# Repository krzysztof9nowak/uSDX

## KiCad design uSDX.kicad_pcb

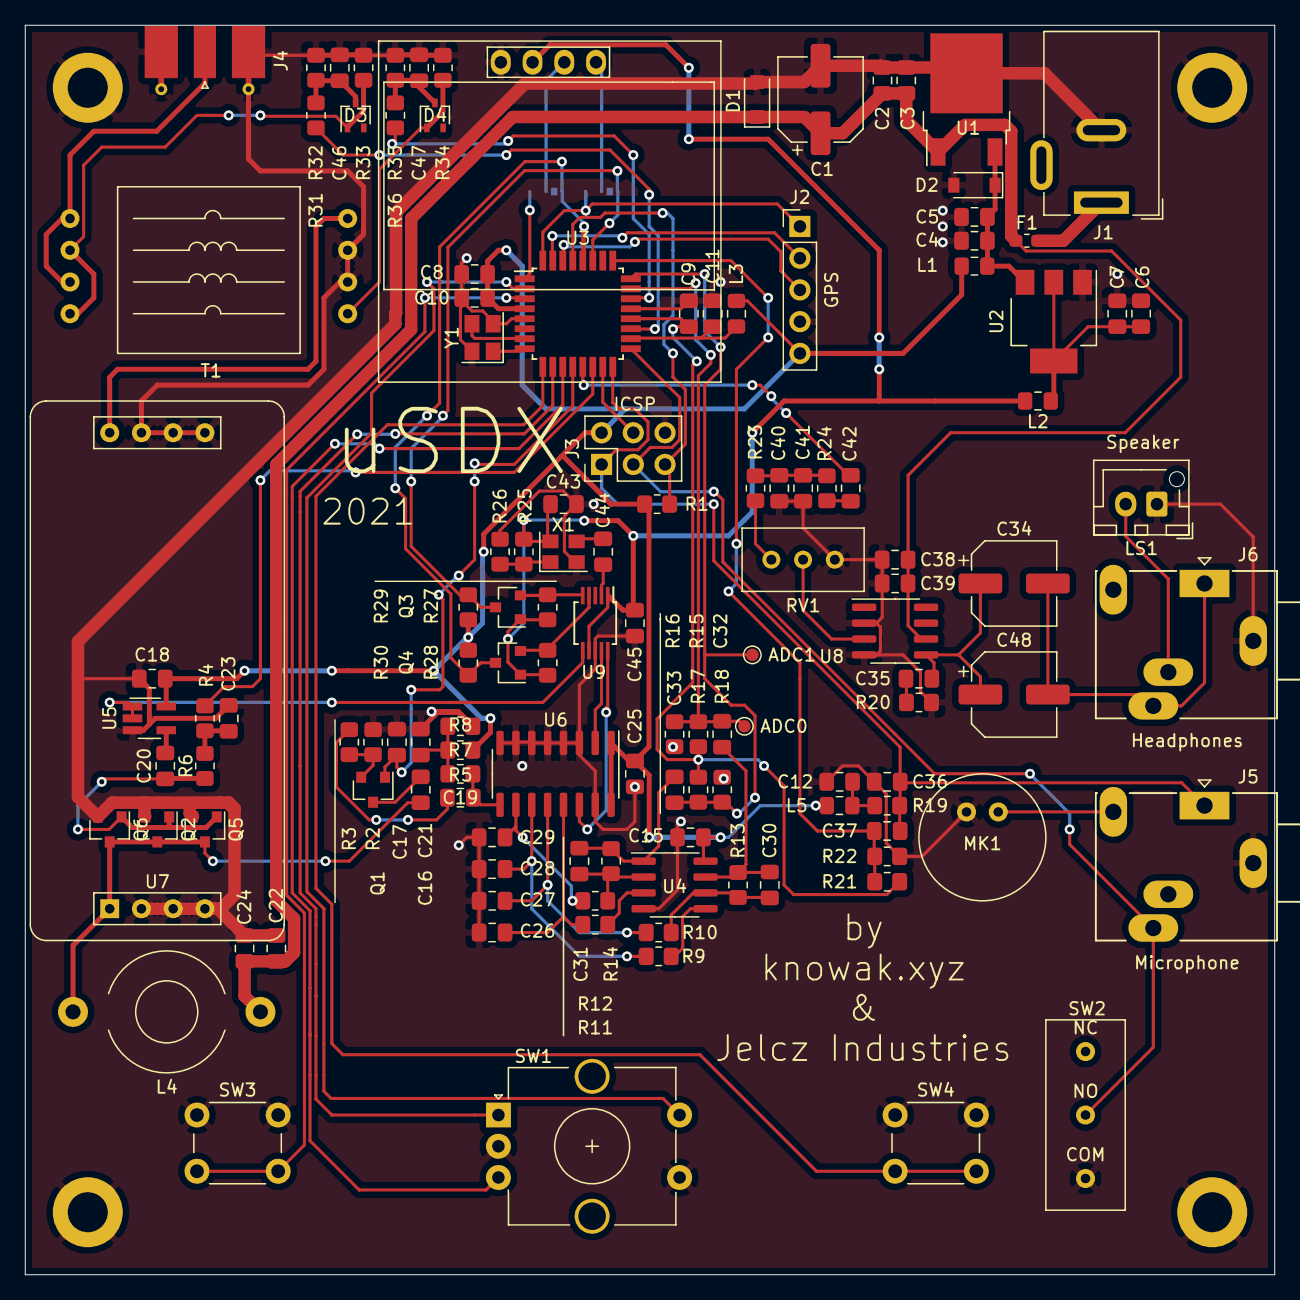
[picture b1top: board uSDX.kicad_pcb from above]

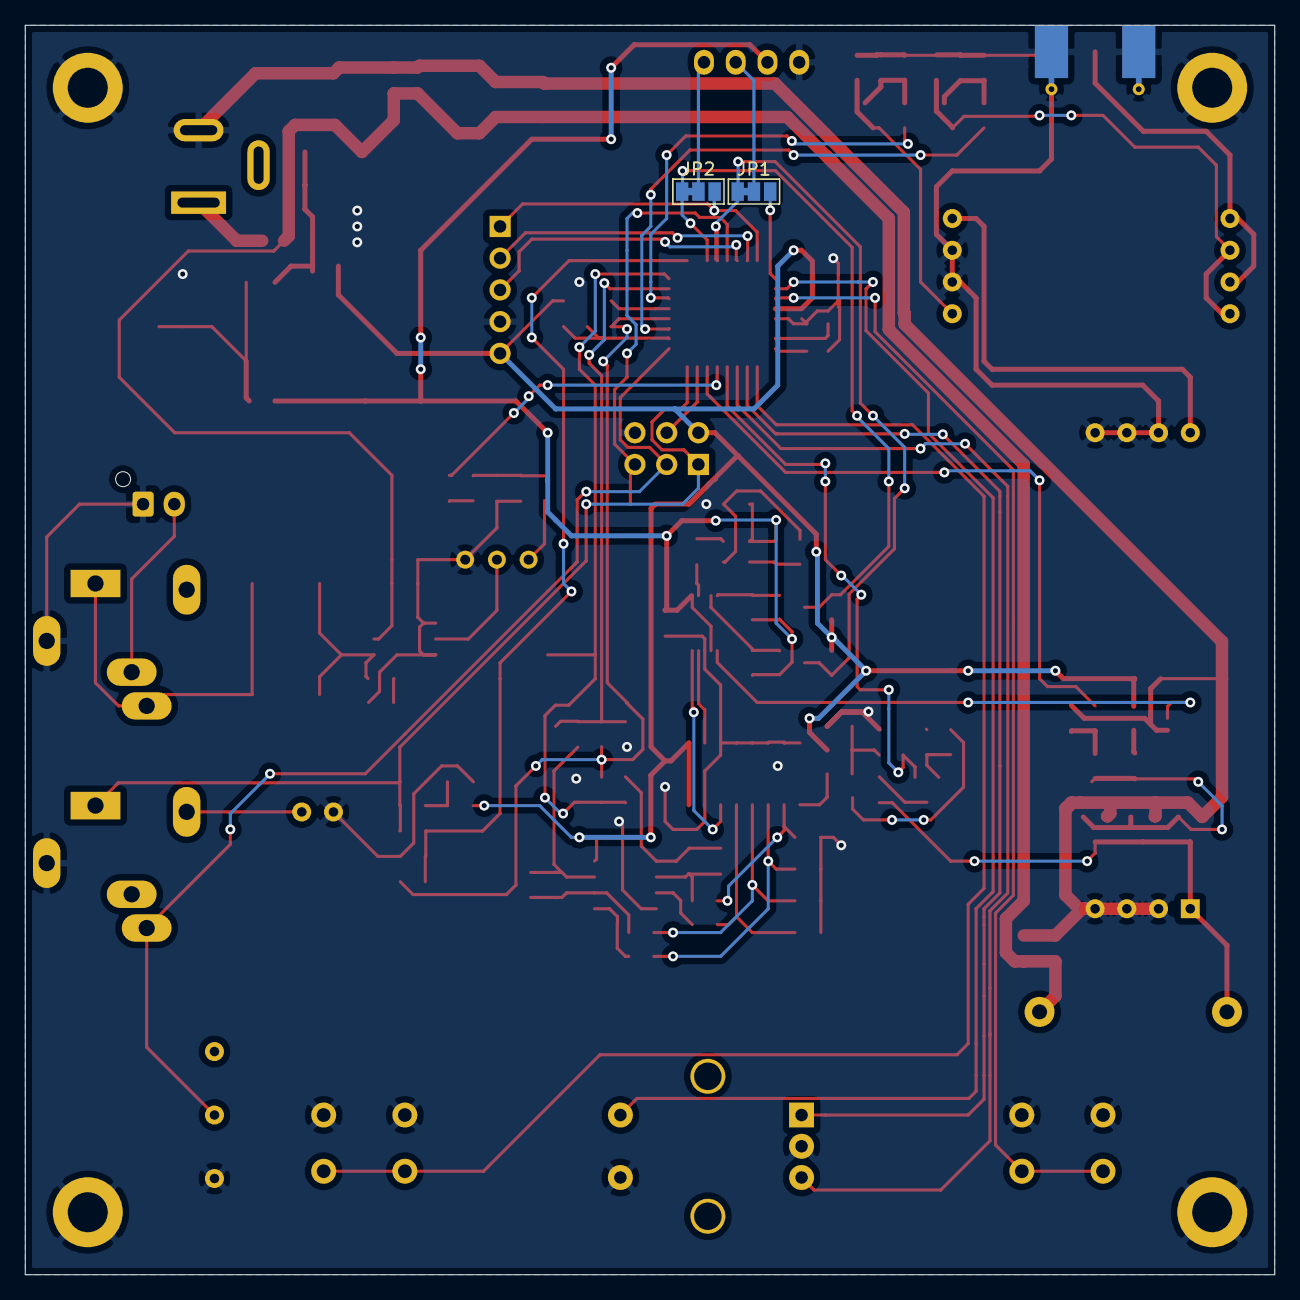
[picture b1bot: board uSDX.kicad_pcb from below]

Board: 2 copper layers, 100.0 x 100.0 mm, 128 parts (2 on the bottom side), 79 nets.

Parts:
ADC0, ADC1: TestPoint_Pad_D1.0mm
Brd1: SSD1306; 128x64OLED
C1, C34, C48: 100u; CP_Elec_6.3x7.7
C2, C5, C7, C10, C22, C39, C42: 10u; C_0805_2012Metric_Pad1.18x1.45mm_HandSolder
C3, C4, C6, C8, C9, C11, C12, C15, C18, C21, C24, C25, C32, C33, C37, C38, C40, C41, C43, C44, C45, C46, C47: 100n; C_0805_2012Metric_Pad1.18x1.45mm_HandSolder
C16, C17, C19, C20, C23, C36: 10n; C_0805_2012Metric_Pad1.18x1.45mm_HandSolder
C26, C27, C28, C29: 470n; C_0805_2012Metric_Pad1.18x1.45mm_HandSolder
C30, C31: 1n; C_0805_2012Metric_Pad1.18x1.45mm_HandSolder
C35: 47n; C_0805_2012Metric_Pad1.18x1.45mm_HandSolder
D1: SK14WA; D_SOD-123F
D2: BZT52B5V6; D_SOD-123
D3, D4: BAT54W; SOT-323_SC-70
F1: 1A; Fuse_0603_1608Metric_Pad1.05x0.95mm_HandSolder
J1: Jack-DC; BarrelJack_Wuerth_6941xx301002
J2: GPS_CONN; PinHeader_1x05_P2.54mm_Vertical
J3: ICSP; PinHeader_2x03_P2.54mm_Vertical
J4: SMA; SMA_Molex_73251-2120_EdgeMount_Horizontal
J5: Mic; Jack_3.5mm_Ledino_KB3SPRS_Horizontal
J6: Headphones; Jack_3.5mm_Ledino_KB3SPRS_Horizontal
JP1: SCL; SolderJumper-3_P1.3mm_Bridged12_Pad1.0x1.5mm_NumberLabels
JP2: SDA; SolderJumper-3_P1.3mm_Bridged12_Pad1.0x1.5mm_NumberLabels
L1, L2, L3, L5: 100uH; L_0805_2012Metric_Pad1.15x1.40mm_HandSolder
L4: FT-37-43; L_Toroid_Horizontal_D9.5mm_P15.00mm_Diameter10-5mm_Amidon-T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
LS1: Speaker; JST_XH_B2B-XH-AM_1x02_P2.50mm_Vertical
MK1: Mic; Electret_9.7mm
Q1, Q3, Q4: 2N7002; SOT-23
Q2, Q5, Q6: IRLML2060; SOT-23
R1, R4, R6, R7, R8, R15, R16, R17, R18, R19, R21, R22, R25, R26, R31, R36: 10k; R_0805_2012Metric_Pad1.20x1.40mm_HandSolder
R2, R5: 1k; R_0805_2012Metric_Pad1.20x1.40mm_HandSolder
R3, R33, R34: 50; R_0805_2012Metric_Pad1.20x1.40mm_HandSolder
R9, R10, R11, R12: 100; R_0805_2012Metric_Pad1.20x1.40mm_HandSolder
R13, R14: 82k; R_0805_2012Metric_Pad1.20x1.40mm_HandSolder
R20: 10; R_0805_2012Metric_Pad1.20x1.40mm_HandSolder
R23: 0; R_0805_2012Metric_Pad1.20x1.40mm_HandSolder
R24: 270; R_0805_2012Metric_Pad1.20x1.40mm_HandSolder
R27, R28, R29, R30: 4k7; R_0805_2012Metric_Pad1.20x1.40mm_HandSolder
R32, R35: 470k; R_0805_2012Metric_Pad1.20x1.40mm_HandSolder
RV1: 10k; Potentiometer_Bourns_3296W_Vertical
SW1: Rotary_Encoder_Switch; RotaryEncoder_Alps_EC12E-Switch_Vertical_H20mm_CircularMoun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
SW2: PTT; Limit
SW3: Left; SW_PUSH_6mm
SW4: Right; SW_PUSH_6mm
T1: SWR; SWR_BN-43-202
U1: L7805; TO-252-2
U2: LD1117S33TR_SOT223; SOT-223-3_TabPin2
U3: ATmega328PB-AU; TQFP-32_7x7mm_P0.8mm
U4: LM4562; SOIC-8_3.9x4.9mm_P1.27mm
U5: 74AHCT1G00; SOT-23-5_HandSoldering
U6: SN74CBT3253; SOIC-16_3.9x9.9mm_P1.27mm
U7: Filter
U8: LM386; SOIC-8_3.9x4.9mm_P1.27mm
U9: Si5351A-B-GT; MSOP-10_3x3mm_P0.5mm
X1: FT3HNBPK27.0-T1; Oscillator_SMD_Abracon_ASE-4Pin_3.2x2.5mm
Y1: 20MHz; Crystal_SMD_3225-4Pin_3.2x2.5mm

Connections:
+3V3: Brd1.2, C43.2, C45.2, L2.2, Q3.1, Q4.1, R25.1, R27.1, R28.1, U9.1, U9.7, X1.4
+5VA: C11.2, L3.1, U3.18
+12V: C1.1, C2.2, C3.2, C22.1, C24.1, C38.1, C39.1, D1.1, F1.1, L4.1, U1.1, U8.6
/PLL/CLK_I: U6.14, U9.10
/PLL/CLK_Q: U6.2, U9.9
/PLL/CLK_TX: U5.1, U5.2, U9.6
/RF/RF: T1.3, U7.2
/SWR/RF_OUT: J4.1, T1.1
ADC0: C32.1, R15.1, R16.2, U3.23
ADC1: C33.1, R17.1, R18.2, U3.24
ADC2: C37.2, R21.2, R22.1, U3.25
ADC6: R31.1, U3.19
ADC7: R36.1, U3.22
AREF: C9.2, R15.2, R17.2, R21.1, U3.20
GND: Brd1.1, C1.2, C2.1, C3.1, C4.1, C5.1, C6.1, C7.1, C8.1, C9.1, C10.1, C11.1, C12.2, C15.2, C17.2, C18.2, C21.2, C22.2, C23.2, C24.2, C25.2, C26.2, C27.2, C28.2, C29.2, C36.1, C38.2, C39.2, C40.2, C41.2, C43.1, C45.1, C46.2, C47.2, D1.2, D2.2, J1.2, J2.4, J3.6, J4.2, J5.S, J6.S, LS1.1, MK1.1, Q2.2, Q5.2, Q6.2, R2.2, R8.2, R16.1, R18.1, R20.2, R22.2, R26.2, R32.1, R33.2, R34.2, R35.1, RV1.1, SW1.C, SW1.S2, SW2.1, SW3.1, SW4.1, T1.4, U1.2, U2.1, U3.5, U3.21, U4.4, U5.3, U6.3, U6.4, U6.5, U6.6, U6.7, U6.8, U6.15, U7.3, U8.2, U8.4, U9.8, X1.2, Y1.2, Y1.4
unnamed: Brd1.3, JP1.2
unnamed: Brd1.4, JP2.2
unnamed: C4.2, C5.2, D2.1, L1.1, U1.3, U2.3
unnamed: C6.2, C7.2, L2.1, U2.2
unnamed: C12.1, L5.1, R19.1
unnamed: C16.1, Q1.3
unnamed: C16.2, L4.2, Q2.3, Q5.3, Q6.3, U7.1
unnamed: C19.1, R5.1, U6.9
unnamed: C19.2, R3.1
unnamed: C20.1, Q2.1, Q5.1, Q6.1, R6.1
unnamed: C20.2, U5.4
unnamed: C21.1, R5.2, R7.2, R8.1
unnamed: C23.1, R4.1, R6.2
unnamed: C26.1, R11.2, U6.13
unnamed: C27.1, R10.2, U6.12
unnamed: C28.1, R9.2, U6.11
unnamed: C29.1, R12.2, U6.10
unnamed: C30.1, C32.2, R13.1, U4.7
unnamed: C30.2, R10.1, R13.2, U4.6
unnamed: C31.1, C33.2, R14.1, U4.1
unnamed: C31.2, R12.1, R14.2, U4.2
unnamed: C34.1, C35.2, C48.1, U8.5
unnamed: C34.2, C48.2, J6.R, J6.T
unnamed: C35.1, R20.1
unnamed: C40.1, C41.1, R23.1, R24.2
unnamed: C42.2, R24.1
unnamed: C44.1, X1.3
unnamed: C44.2, U9.2
unnamed: C46.1, D3.3, R31.2, R32.2
unnamed: C47.1, D4.3, R35.2, R36.2
unnamed: D3.1, R33.1, T1.2
unnamed: D4.1, R34.1, T1.5
unnamed: F1.2, J1.1
unnamed: J5.TN, MK1.2
unnamed: J6.RN, LS1.2
unnamed: Q1.2, R2.1, R3.2
unnamed: Q3.2, R27.2, U9.5
unnamed: Q4.2, R28.2, U9.4
unnamed: R9.1, U4.5
unnamed: R11.1, U4.3
unnamed: R23.2, RV1.3
unnamed: R25.2, R26.1, X1.1
unnamed: RV1.2, U8.3
unnamed: U3.7, Y1.3
unnamed: U3.8, Y1.1
PB0: C17.1, Q1.1, U3.12
PB1: C42.1, U3.13
PB2: R4.2, U3.14
PB3: J3.4, U3.15
PB4: C36.2, C37.1, J3.1, J5.T, R19.2, U3.16
PB5: J3.3, J5.R, SW2.2, U3.17
PD2: J2.1, JP2.3, U3.32
PD3: JP1.3, U3.1
PD4: SW1.S1, U3.2
PD5: SW4.2, U3.9
PD6: SW1.A, U3.10
PD7: SW1.B, U3.11
PE0: SW3.2, U3.3
RST: J3.5, R1.2, U3.29
RX: J2.3, U3.30
SCL: JP1.1, Q4.3, R30.2, U3.28
SDA: JP2.1, Q3.3, R29.2, U3.27
TX: J2.2, U3.31
VCC: C8.2, C10.2, C15.1, C18.1, C25.1, J2.5, J3.2, L1.2, L3.2, L5.2, R1.1, R7.1, R29.1, R30.1, U3.4, U4.8, U5.5, U6.1, U6.16

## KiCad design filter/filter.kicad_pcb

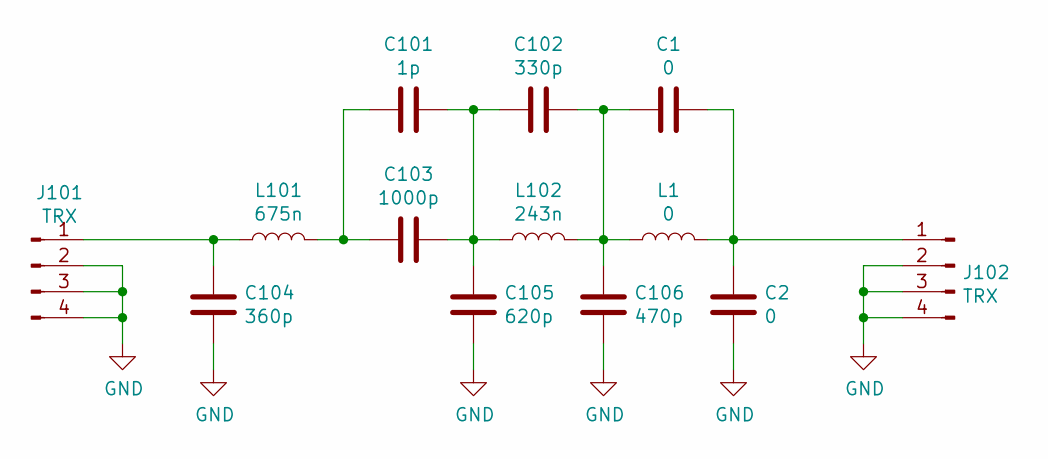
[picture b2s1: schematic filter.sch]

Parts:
C1, C2: 0; C_0805_2012Metric_Pad1.18x1.45mm_HandSolder
C101: 1p; C_0805_2012Metric_Pad1.18x1.45mm_HandSolder
C102: 330p; C_0805_2012Metric_Pad1.18x1.45mm_HandSolder
C103: 1000p; C_0805_2012Metric_Pad1.18x1.45mm_HandSolder
C104: 360p; C_0805_2012Metric_Pad1.18x1.45mm_HandSolder
C105: 620p; C_0805_2012Metric_Pad1.18x1.45mm_HandSolder
C106: 470p; C_0805_2012Metric_Pad1.18x1.45mm_HandSolder
J101, J102: TRX; PinHeader_1x04_P2.54mm_Vertical
L1: 0; L_Toroid_Horizontal_D9.5mm_P15.00mm_Diameter10-5mm_Amidon-T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
L101: 675n; L_Toroid_Horizontal_D9.5mm_P15.00mm_Diameter10-5mm_Amidon-T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
L102: 243n; L_Toroid_Horizontal_D9.5mm_P15.00mm_Diameter10-5mm_Amidon-T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

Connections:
GND: C2.1, C104.2, C105.1, C106.1, J101.2, J101.3, J101.4, J102.2, J102.3, J102.4
unnamed: C1.1, C102.2, C106.2, L1.1, L102.2
unnamed: C1.2, C2.2, J102.1, L1.2
unnamed: C101.1, C102.1, C103.1, C105.2, L102.1
unnamed: C101.2, C103.2, L101.2
unnamed: C104.1, J101.1, L101.1

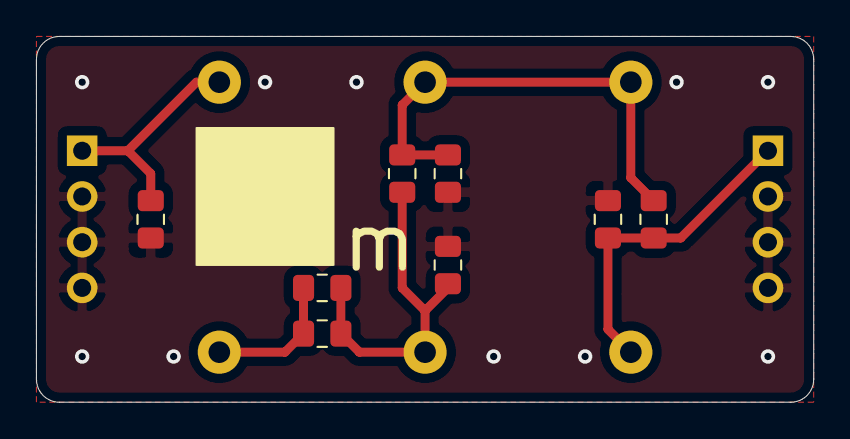
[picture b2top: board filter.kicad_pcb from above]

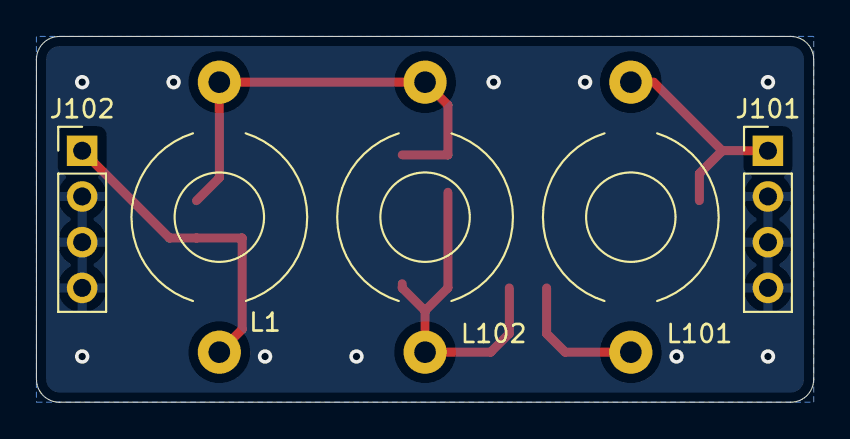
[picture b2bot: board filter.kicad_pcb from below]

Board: 2 copper layers, 43.2 x 20.3 mm, 13 parts (5 on the bottom side), 6 nets.

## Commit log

2021-06-13 Initial
2021-06-13 filter backup
2021-06-15 PCB in progress, filter screwed up
2021-06-16 Work on PCB
2021-06-16 Reverted filter
2021-06-16 Filter updated
2021-06-16 Almost final PCB
2021-06-23 Final
2021-06-23 ibom
